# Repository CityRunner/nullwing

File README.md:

# nullwing

Through hole mechanical keyboard with rotary encoder

# IMAGES

# BOM
| Value | Designator | Footprint | Quantity |
|---|---|---|---|
| Battery | BT1 | JST_PH_S2B-PH-K_1x02_P2.00mm_Horizontal | 1 |
| Diode | D1 - D40 | Diode_DO-35 | 40 |
| Keyswitch | S1 - S40 | Choc_Mini_1.00u | 40 |
| Power Switch | SW1 | SW_CuK_OS102011MA1QN1_SPDT_Angled | 1 |
| Reset Switch | SW2 | SW_TH_Tactile_Omron_B3F-10xx | 1 |
| RotaryEncoder_Switch | SW3 | RotaryEncoder_Alps_EC12E-Switch_Vertical_H20mm | 1 |
| Nice_Nano_V2 | U1 | Nice_Nano_V2 | 1 |
| ChosFox CFX Keycaps | - | - | 40 |
| 3.7V Lipo 301230 Battery | - | - | 1 |
| SMC-1-12-1-GT‎ Socket | - | - | 2 |

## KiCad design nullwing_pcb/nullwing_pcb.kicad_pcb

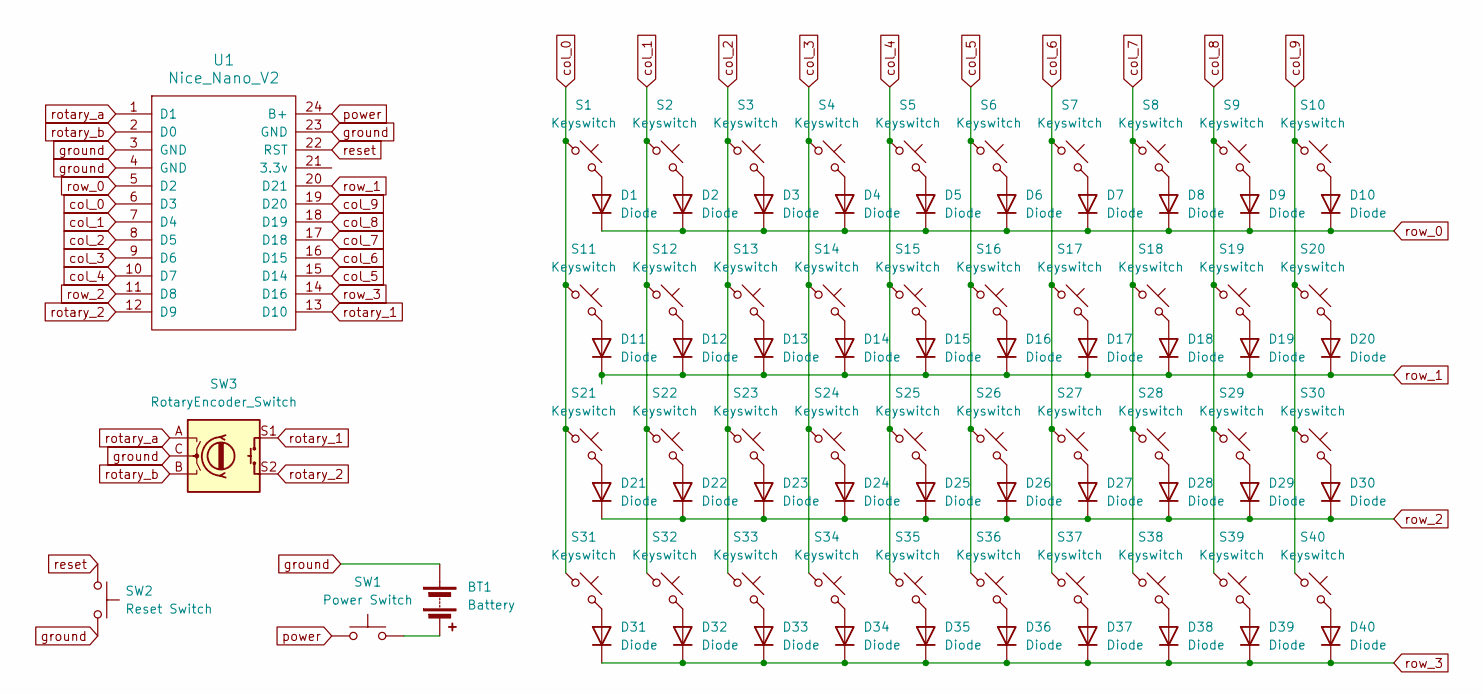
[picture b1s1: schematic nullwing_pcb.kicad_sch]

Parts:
BT1: Battery; JST_PH_S2B-PH-K_1x02_P2.00mm_Horizontal
D1, D2, D3, D4, D5, D6, D7, D8, D9, D10, D11, D12, D13, D14, D15, D16, D17, D18, D19, D20, D21, D22, D23, D24, D25, D26, D27, D28, D29, D30, D31, D32, D33, D34, D35, D36, D37, D38, D39, D40: Diode; Diode_DO-35
S1, S2, S3, S4, S5, S6, S7, S8, S9, S10, S11, S12, S13, S14, S15, S16, S17, S18, S19, S20, S21, S22, S23, S24, S25, S26, S27, S28, S29, S30, S31, S32, S33, S34, S35, S36, S37, S38, S39, S40: Keyswitch; Choc_Mini_1.00u
SW1: Power Switch; SW_CuK_OS102011MA1QN1_SPDT_Angled
SW2: Reset Switch; SW_TH_Tactile_Omron_B3F-10xx
SW3: RotaryEncoder_Switch; RotaryEncoder_Alps_EC12E-Switch_Vertical_H20mm
U1: Nice_Nano_V2

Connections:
unnamed: BT1.2 (-), SW1.2
unnamed: D1.2 (A), S1.2
unnamed: D2.2 (A), S2.2
unnamed: D3.2 (A), S3.2
unnamed: D4.2 (A), S4.2
unnamed: D5.2 (A), S5.2
unnamed: D6.2 (A), S6.2
unnamed: D7.2 (A), S7.2
unnamed: D8.2 (A), S8.2
unnamed: D9.2 (A), S9.2
unnamed: D10.2 (A), S10.2
unnamed: D11.2 (A), S11.2
unnamed: D12.2 (A), S12.2
unnamed: D13.2 (A), S13.2
unnamed: D14.2 (A), S14.2
unnamed: D15.2 (A), S15.2
unnamed: D16.2 (A), S16.2
unnamed: D17.2 (A), S17.2
unnamed: D18.2 (A), S18.2
unnamed: D19.2 (A), S19.2
unnamed: D20.2 (A), S20.2
unnamed: D21.2 (A), S21.2
unnamed: D22.2 (A), S22.2
unnamed: D23.2 (A), S23.2
unnamed: D24.2 (A), S24.2
unnamed: D25.2 (A), S25.2
unnamed: D26.2 (A), S26.2
unnamed: D27.2 (A), S27.2
unnamed: D28.2 (A), S28.2
unnamed: D29.2 (A), S29.2
unnamed: D30.2 (A), S30.2
unnamed: D31.2 (A), S31.2
unnamed: D32.2 (A), S32.2
unnamed: D33.2 (A), S33.2
unnamed: D34.2 (A), S34.2
unnamed: D35.2 (A), S35.2
unnamed: D36.2 (A), S36.2
unnamed: D37.2 (A), S37.2
unnamed: D38.2 (A), S38.2
unnamed: D39.2 (A), S39.2
unnamed: D40.2 (A), S40.2
col_0: S1.1, S11.1, S21.1, S31.1, U1.6 (D3)
col_1: S2.1, S12.1, S22.1, S32.1, U1.7 (D4)
col_2: S3.1, S13.1, S23.1, S33.1, U1.8 (D5)
col_3: S4.1, S14.1, S24.1, S34.1, U1.9 (D6)
col_4: S5.1, S15.1, S25.1, S35.1, U1.10 (D7)
col_5: S6.1, S16.1, S26.1, S36.1, U1.15 (D14)
col_6: S7.1, S17.1, S27.1, S37.1, U1.16 (D15)
col_7: S8.1, S18.1, S28.1, S38.1, U1.17 (D18)
col_8: S9.1, S19.1, S29.1, S39.1, U1.18 (D19)
col_9: S10.1, S20.1, S30.1, S40.1, U1.19 (D20)
ground: BT1.1 (+), SW2.2, SW3.C, U1.3 (GND), U1.4 (GND), U1.23 (GND)
power: SW1.1, U1.24 (B+)
reset: SW2.1, U1.22 (RST)
rotary_1: SW3.S1, U1.13 (D10)
rotary_2: SW3.S2, U1.12 (D9)
rotary_a: SW3.A, U1.1 (D1)
rotary_b: SW3.B, U1.2 (D0)
row_0: D1.1 (K), D2.1 (K), D3.1 (K), D4.1 (K), D5.1 (K), D6.1 (K), D7.1 (K), D8.1 (K), D9.1 (K), D10.1 (K), U1.5 (D2)
row_1: D11.1 (K), D12.1 (K), D13.1 (K), D14.1 (K), D15.1 (K), D16.1 (K), D17.1 (K), D18.1 (K), D19.1 (K), D20.1 (K), U1.20 (D21)
row_2: D21.1 (K), D22.1 (K), D23.1 (K), D24.1 (K), D25.1 (K), D26.1 (K), D27.1 (K), D28.1 (K), D29.1 (K), D30.1 (K), U1.11 (D8)
row_3: D31.1 (K), D32.1 (K), D33.1 (K), D34.1 (K), D35.1 (K), D36.1 (K), D37.1 (K), D38.1 (K), D39.1 (K), D40.1 (K), U1.14 (D16)

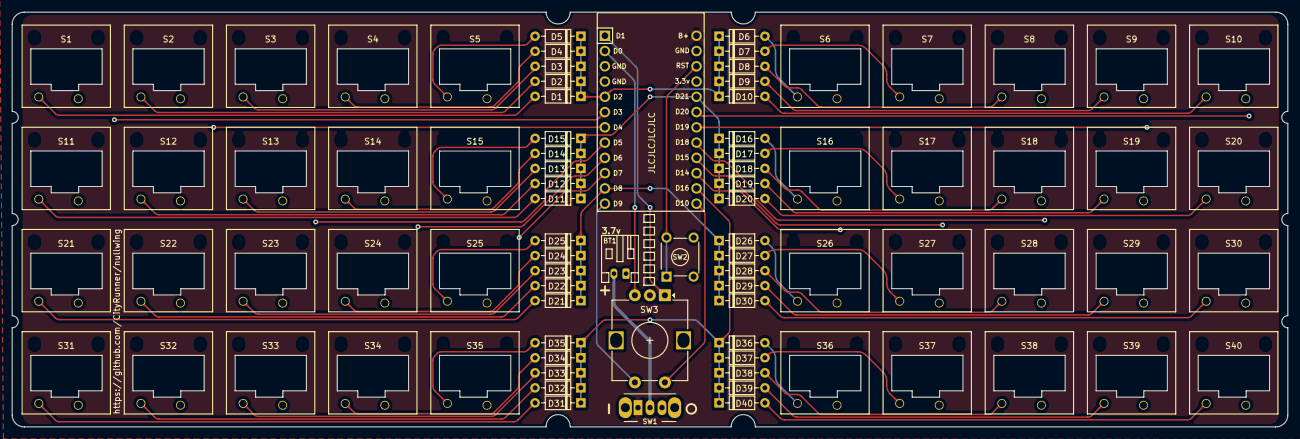
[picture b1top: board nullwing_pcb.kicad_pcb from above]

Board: 2 copper layers, 212.2 x 69.0 mm, 85 parts (0 on the bottom side), 62 nets.

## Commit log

2024-01-21 add project files
2024-01-21 Rename nullwing_schematic
